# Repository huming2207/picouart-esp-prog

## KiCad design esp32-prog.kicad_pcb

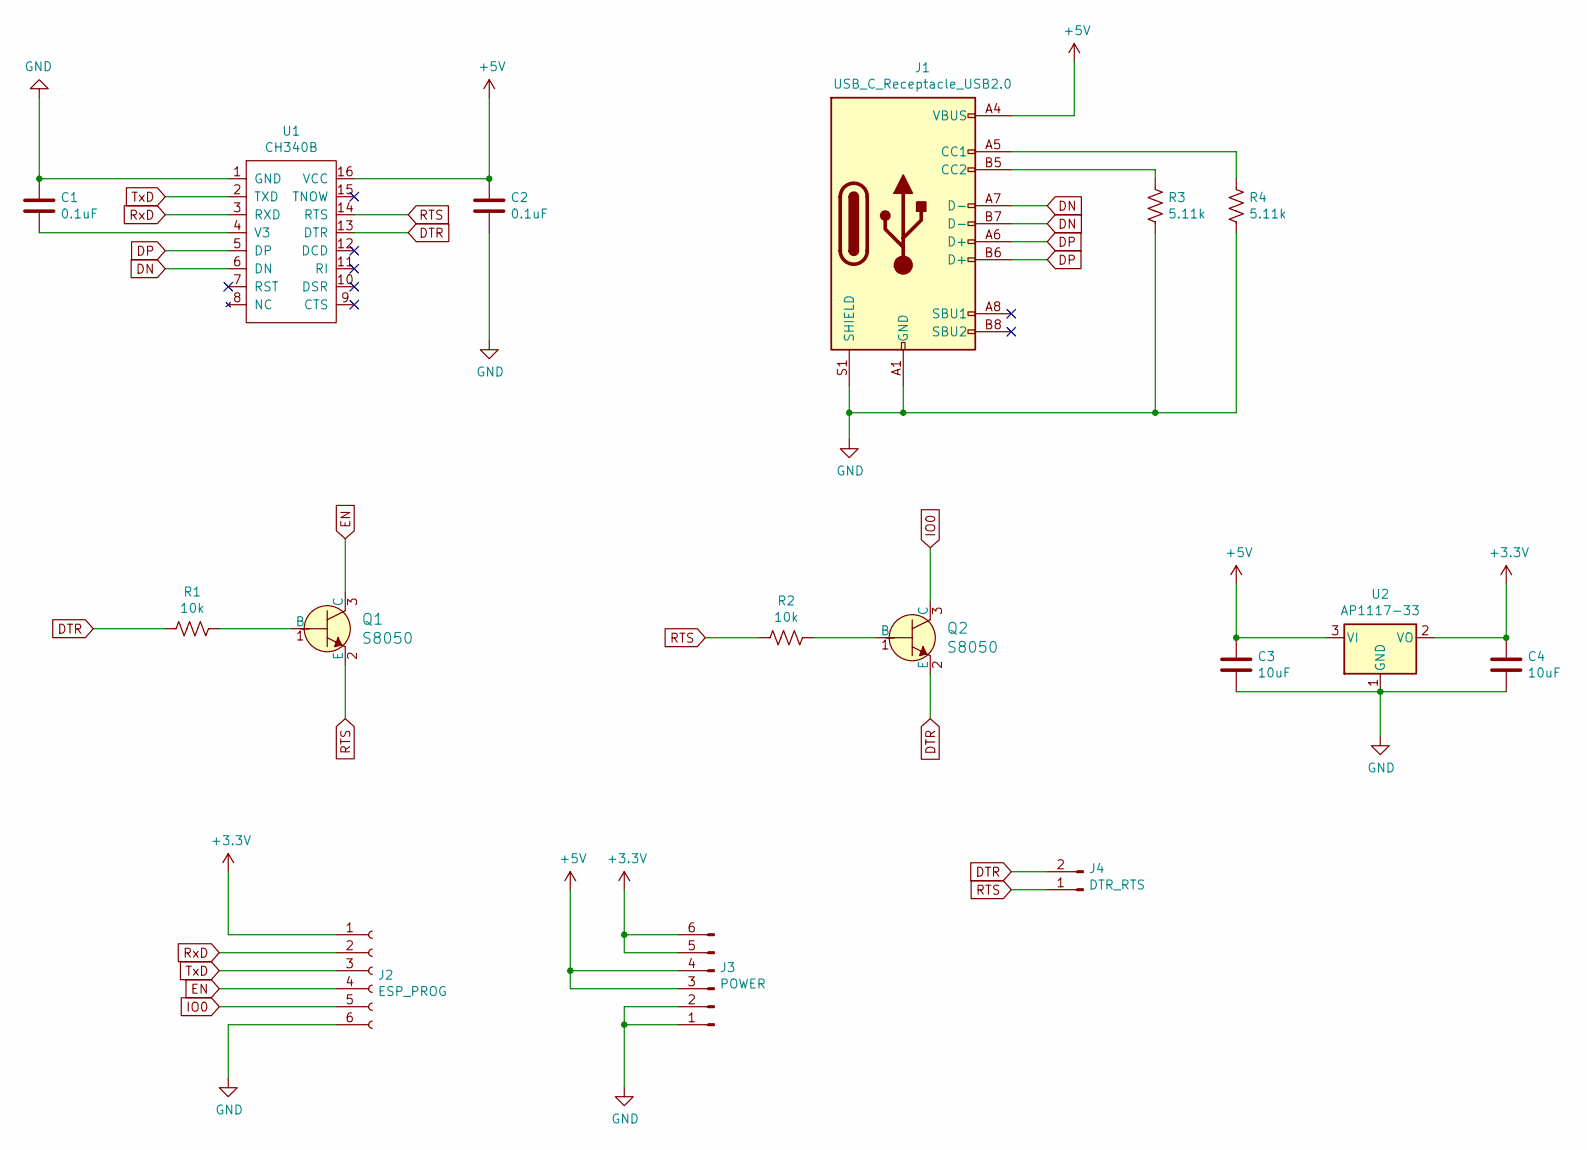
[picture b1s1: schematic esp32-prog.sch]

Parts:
C1, C2: 0.1uF; C_0805_2012Metric_Pad1.18x1.45mm_HandSolder; LCSC C314285
C3, C4: 10uF; C_0805_2012Metric_Pad1.18x1.45mm_HandSolder; LCSC C15850
J1: USB_C_Receptacle_USB2.0; USB_C_Receptacle_HRO_TYPE-C-31-M-12; LCSC C165948
J2: ESP_PROG; PinSocket_1x06_P2.54mm_Vertical
J3: POWER; PinSocket_1x06_P2.54mm_Vertical
J4: DTR_RTS; PinHeader_1x02_P2.54mm_Vertical
Q1, Q2: S8050; SOT-23; MPN MMSS8050-H-TP; Digi-Key_PN MMSS8050-H-TPMSCT-ND
R1, R2: 10k; R_0805_2012Metric_Pad1.20x1.40mm_HandSolder; LCSC C169071
R3, R4: 5.11k; R_0805_2012Metric_Pad1.20x1.40mm_HandSolder; LCSC C204553
U1: CH340B; SO-16_3.9x9.9mm_P1.27mm; LCSC C81010
U2: AP1117-33; SOT-223-3_TabPin2; LCSC C351784

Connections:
+3V3: C4.1, J2.1, J3.5, J3.6, U2.2 (VO)
+5V: C2.1, C3.1, J1.A4 (VBUS), J1.A9 (VBUS), J1.B4 (VBUS), J1.B9 (VBUS), J3.3, J3.4, U1.16 (VCC), U2.3 (VI)
DN: J1.A7 (D-), J1.B7 (D-), U1.6 (DN)
DP: J1.A6 (D+), J1.B6 (D+), U1.5 (DP)
DTR: J4.2, Q2.2 (E), R1.2, U1.13 (DTR)
EN: J2.4, Q1.3 (C)
GND: C1.1, C2.2, C3.2, C4.2, J1.A1 (GND), J1.A12 (GND), J1.B1 (GND), J1.B12 (GND), J1.S1 (SHIELD), J2.6, J3.1, J3.2, R3.2, R4.2, U1.1 (GND), U2.1 (GND)
IO0: J2.5, Q2.3 (C)
unnamed: C1.2, U1.4 (V3)
unnamed: J1.A5 (CC1), R4.1
unnamed: J1.B5 (CC2), R3.1
unnamed: Q1.1 (B), R1.1
unnamed: Q2.1 (B), R2.1
RTS: J4.1, Q1.2 (E), R2.2, U1.14 (RTS)
RxD: J2.2, U1.3 (RXD)
TxD: J2.3, U1.2 (TXD)

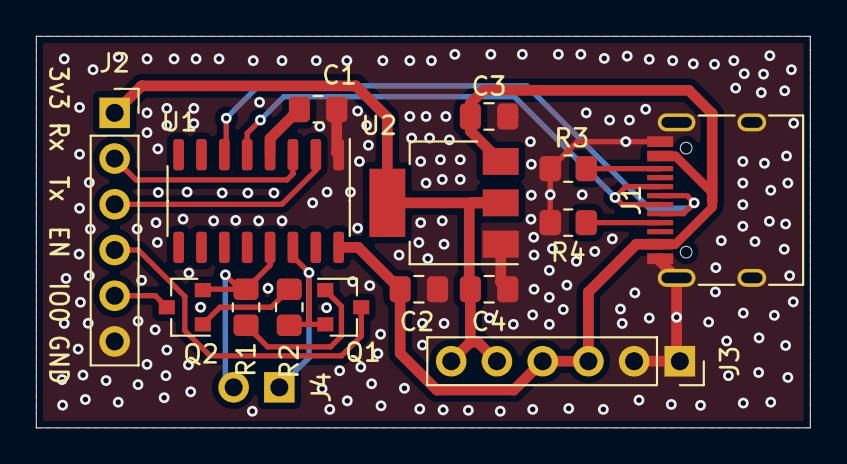
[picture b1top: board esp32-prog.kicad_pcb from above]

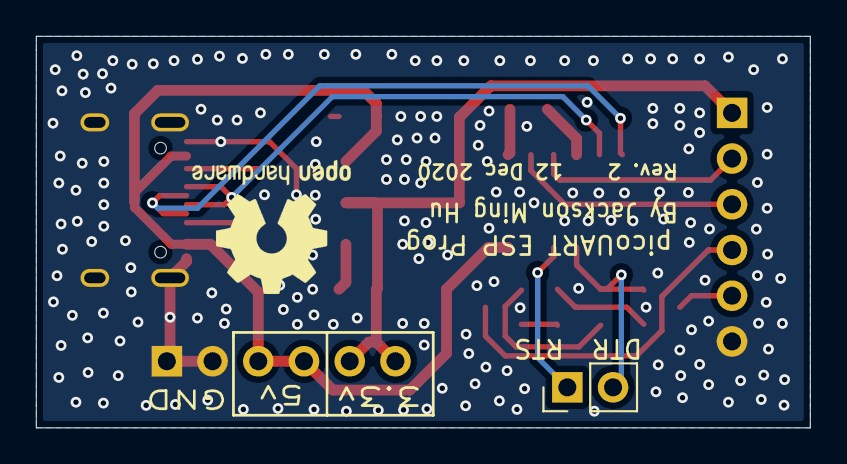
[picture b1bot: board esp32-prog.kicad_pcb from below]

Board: 4 copper layers, 43.0 x 21.8 mm, 17 parts (2 on the bottom side), 16 nets.

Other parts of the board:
LOGO: OSHW-Logo2_9.8x8mm_SilkScreen

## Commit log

2020-12-12 Init
2020-12-12 Finalise Rev 1.2
